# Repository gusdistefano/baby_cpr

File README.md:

# Neonatal CPR Simulator

This repository is available in multiple languages:

- [English](README_EN.md)

- [Español](README_ES.md)

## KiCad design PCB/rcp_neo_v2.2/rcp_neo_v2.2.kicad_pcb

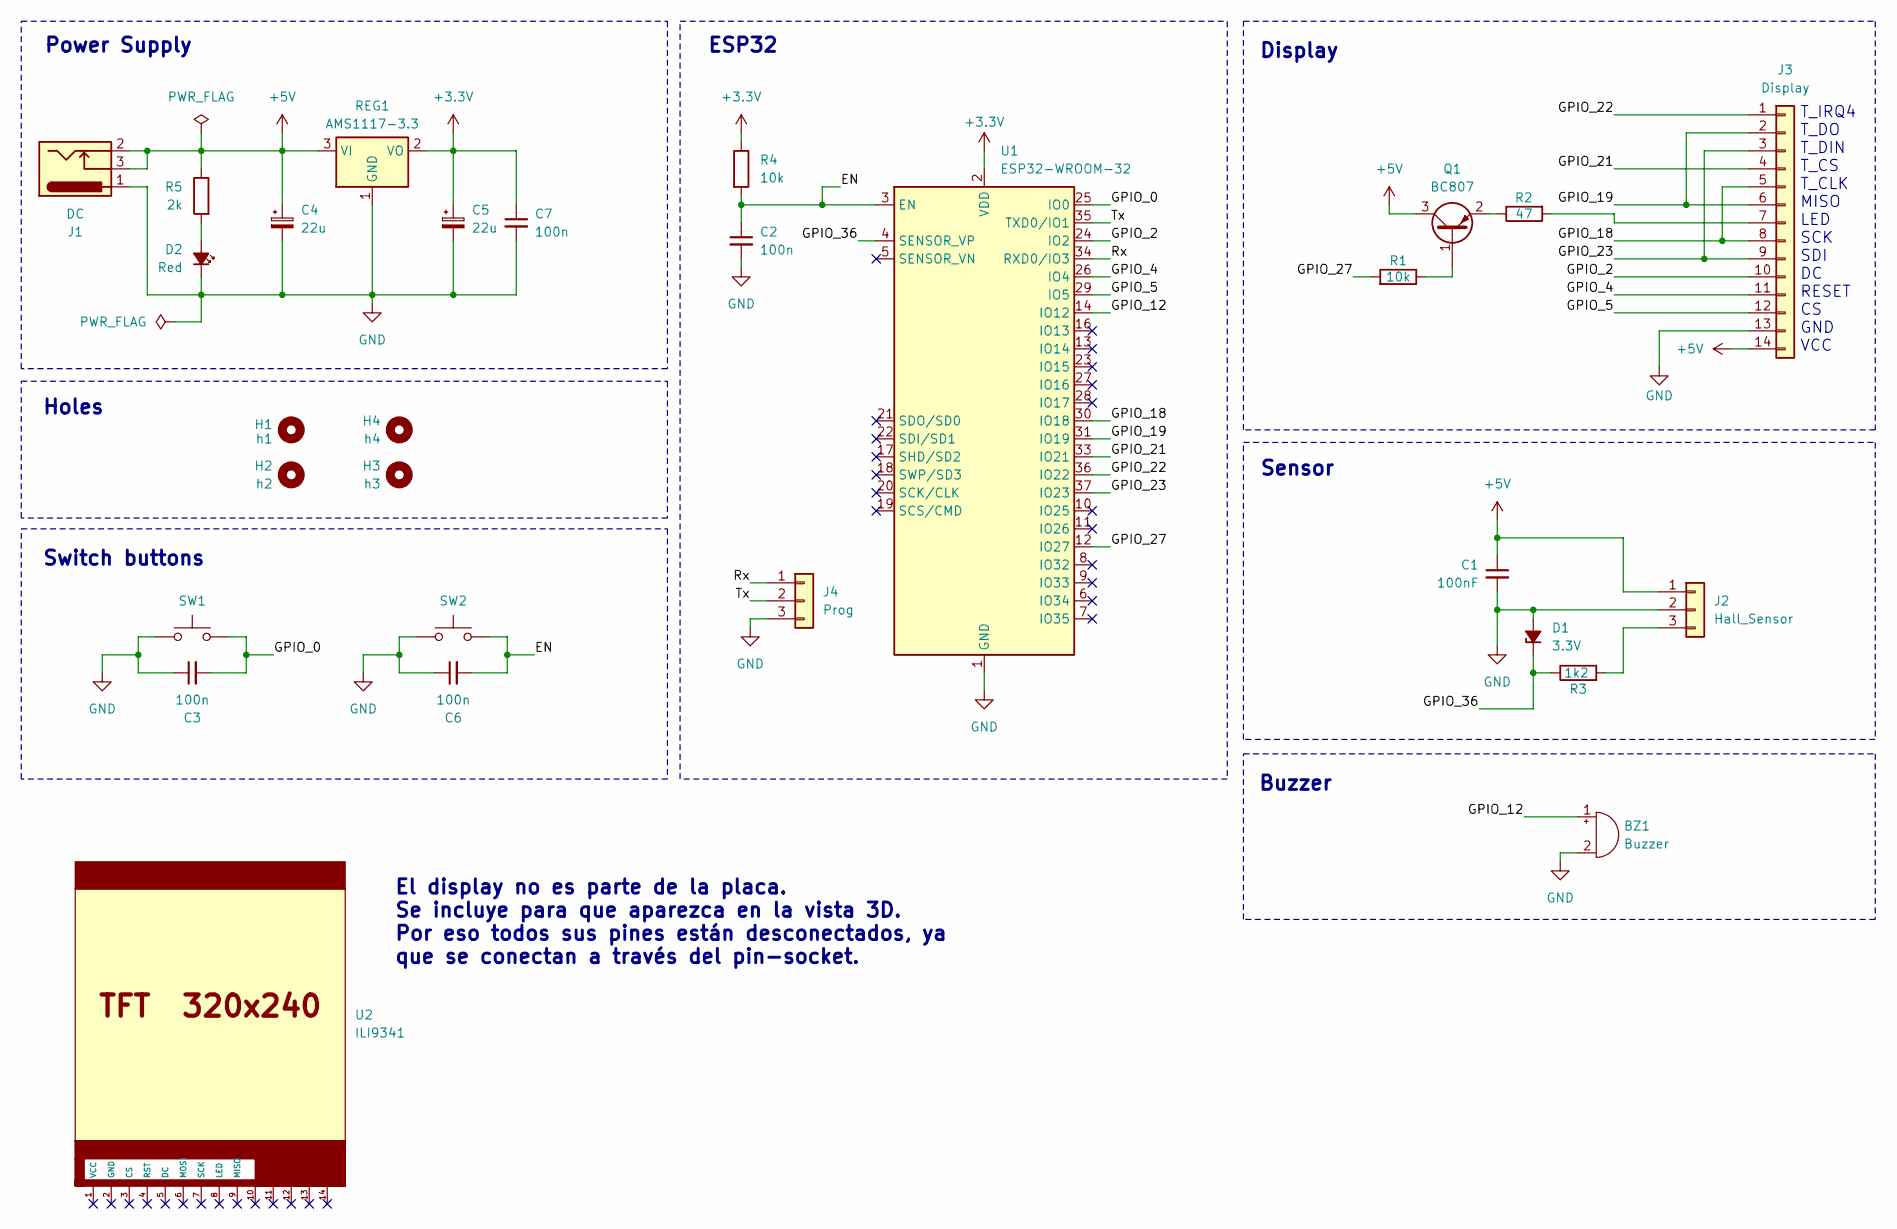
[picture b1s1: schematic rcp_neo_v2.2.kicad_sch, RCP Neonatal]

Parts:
BZ1: Buzzer; Buzzer_12x9.5RM7.6
C1: 100nF; C_1206_3216Metric_Pad1.33x1.80mm_HandSolder
C2, C3, C6, C7: 100n; C_1206_3216Metric_Pad1.33x1.80mm_HandSolder
C4, C5: 22u; CP_Elec_5x4.4
D1: 3.3V; D_DO-35_SOD27_P7.62mm_Horizontal
D2: Red; LED_D3.0mm_Horizontal_O1.27mm_Z2.0mm
H1: h1; MountingHole_3mm
H2: h2; MountingHole_3mm
H3: h3; MountingHole_3mm
H4: h4; MountingHole_3mm
J1: DC; BarrelJack_Horizontal
J2: Hall_Sensor; PinHeader_1x03_P2.54mm_Horizontal
J3: Display; PinSocket_1x14_P2.54mm_Vertical
J4: Prog; PinHeader_1x03_P2.54mm_Horizontal
Q1: BC807; SOT-23
R1, R4: 10k; R_1206_3216Metric_Pad1.30x1.75mm_HandSolder
R2: 47; R_1206_3216Metric_Pad1.30x1.75mm_HandSolder
R3: 1k2; R_1206_3216Metric_Pad1.30x1.75mm_HandSolder
R5: 2k; R_1206_3216Metric_Pad1.30x1.75mm_HandSolder
REG1: AMS1117-3.3; SOT-223-3_TabPin2
SW1, SW2: SW_Push; SW_SPST_B3U-1000P
U1: ESP32-WROOM-32
U2: ILI9341; TFT-320x240_ILI9341_TOUCH

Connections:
+3.3V: C5.1, C7.1, R4.1, REG1.2 (VO), U1.2 (VDD)
+5V: C1.1, C4.1, J1.2, J1.3, J2.1, J3.14, Q1.3 (C), R5.1, REG1.3 (VI)
/EN: C2.1, C6.2, R4.2, SW2.2, U1.3 (EN)
/GPIO_0: C3.2, SW1.2, U1.25 (IO0)
/GPIO_2: J3.10, U1.24 (IO2)
/GPIO_4: J3.11, U1.26 (IO4)
/GPIO_5: J3.12, U1.29 (IO5)
/GPIO_12: BZ1.1 (+), U1.14 (IO12)
/GPIO_18: J3.5, J3.8, U1.30 (IO18)
/GPIO_19: J3.2, J3.6, U1.31 (IO19)
/GPIO_21: J3.4, U1.33 (IO21)
/GPIO_22: J3.1, U1.36 (IO22)
/GPIO_23: J3.3, J3.9, U1.37 (IO23)
/GPIO_27: R1.2, U1.12 (IO27)
/GPIO_36: D1.1 (K), R3.1, U1.4 (SENSOR_VP)
/Rx: J4.1, U1.34 (RXD0/IO3)
/Tx: J4.2, U1.35 (TXD0/IO1)
GND: BZ1.2 (-), C1.2, C2.2, C3.1, C4.2, C5.2, C6.1, C7.2, D1.2 (A), D2.1 (K), J1.1, J2.2, J3.13, J4.3, REG1.1 (GND), SW1.1, SW2.1, U1.1 (GND), U1.15 (GND), U1.38 (GND), U1.39 (GND)
unnamed: D2.2 (A), R5.2
unnamed: J2.3, R3.2
unnamed: J3.7, R2.2
unnamed: Q1.1 (B), R1.1
unnamed: Q1.2 (E), R2.1

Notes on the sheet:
ESP32
El display no es parte de la placa. Se incluye para que aparezca en la vista 3D. Por eso todos sus pines están desconectados, ya que se conectan a través del pin-socket.
Buzzer
Switch buttons
Sensor
Display
T_IRQ4 T_DO T_DIN T_CS T_CLK MISO LED SCK SDI DC RESET CS GND VCC
Holes
Power Supply

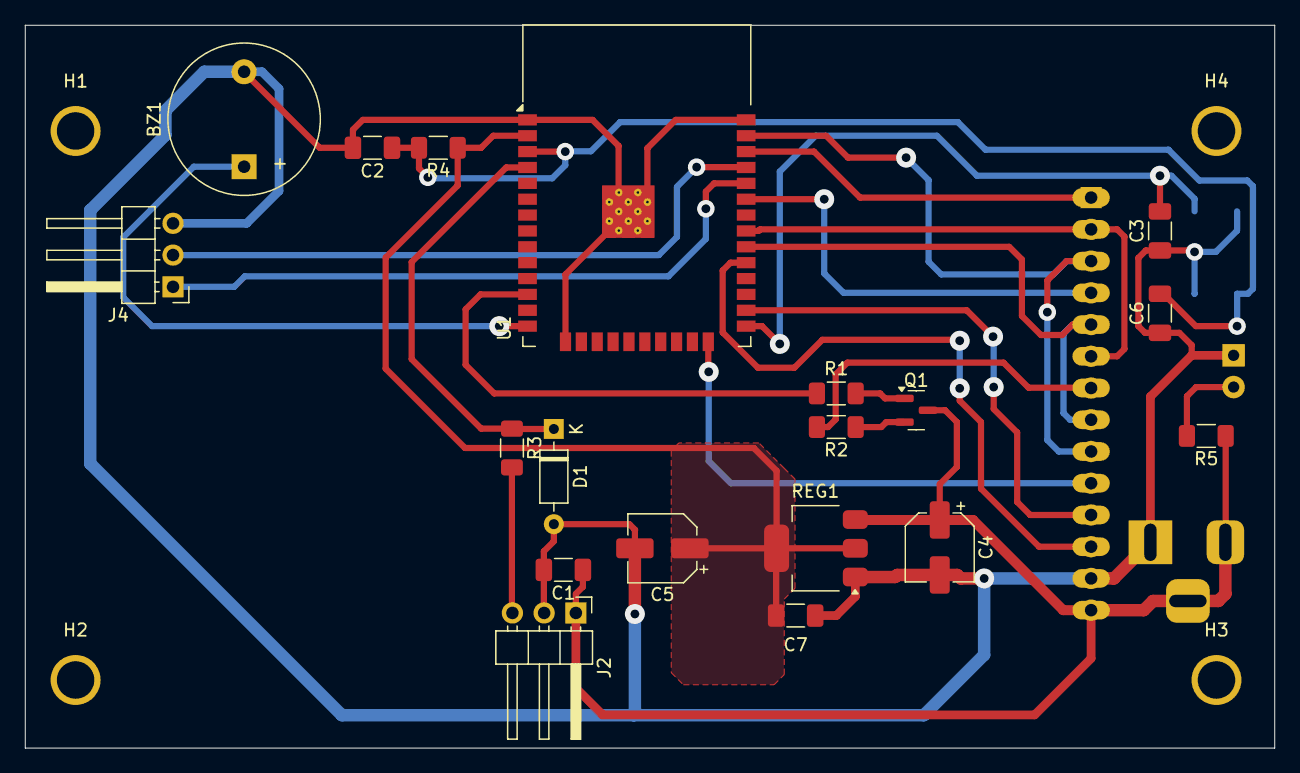
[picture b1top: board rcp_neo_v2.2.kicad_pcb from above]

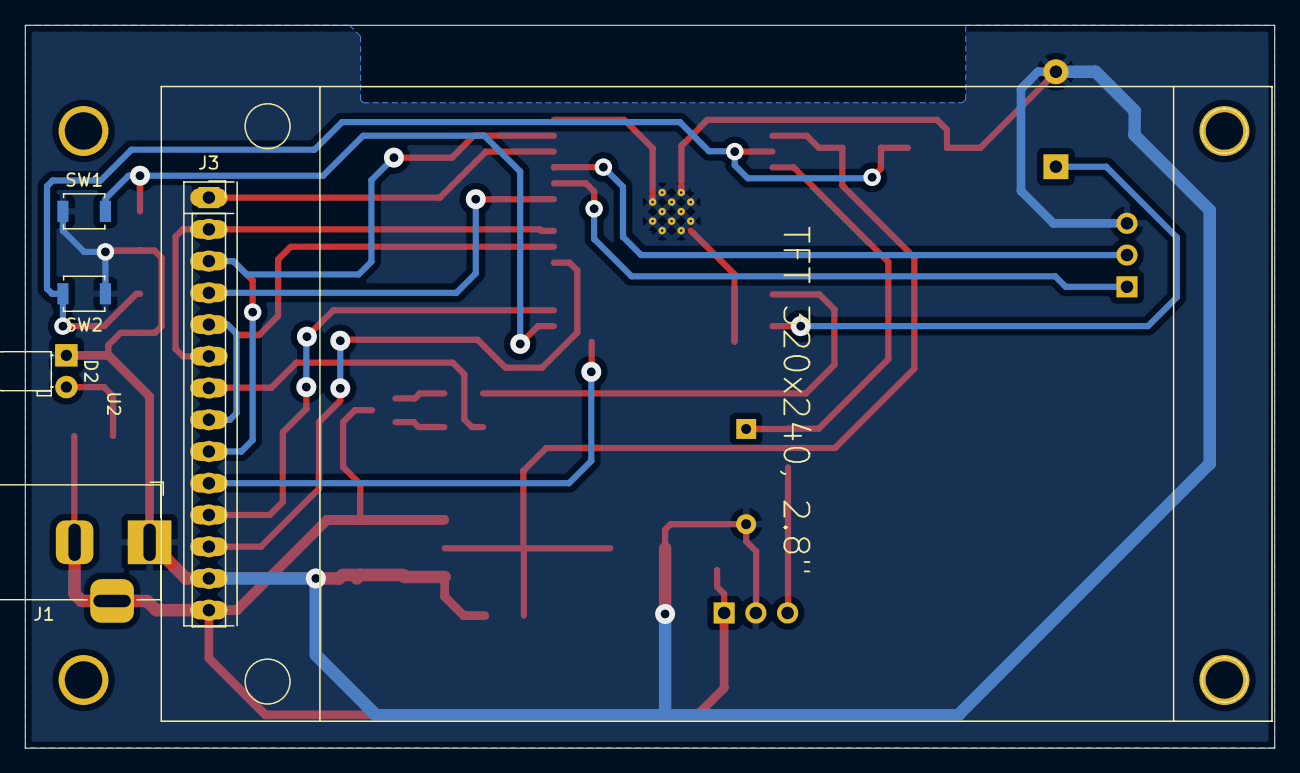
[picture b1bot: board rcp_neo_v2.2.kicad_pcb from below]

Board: 2 copper layers, 100.0 x 57.9 mm, 29 parts (6 on the bottom side), 23 nets.

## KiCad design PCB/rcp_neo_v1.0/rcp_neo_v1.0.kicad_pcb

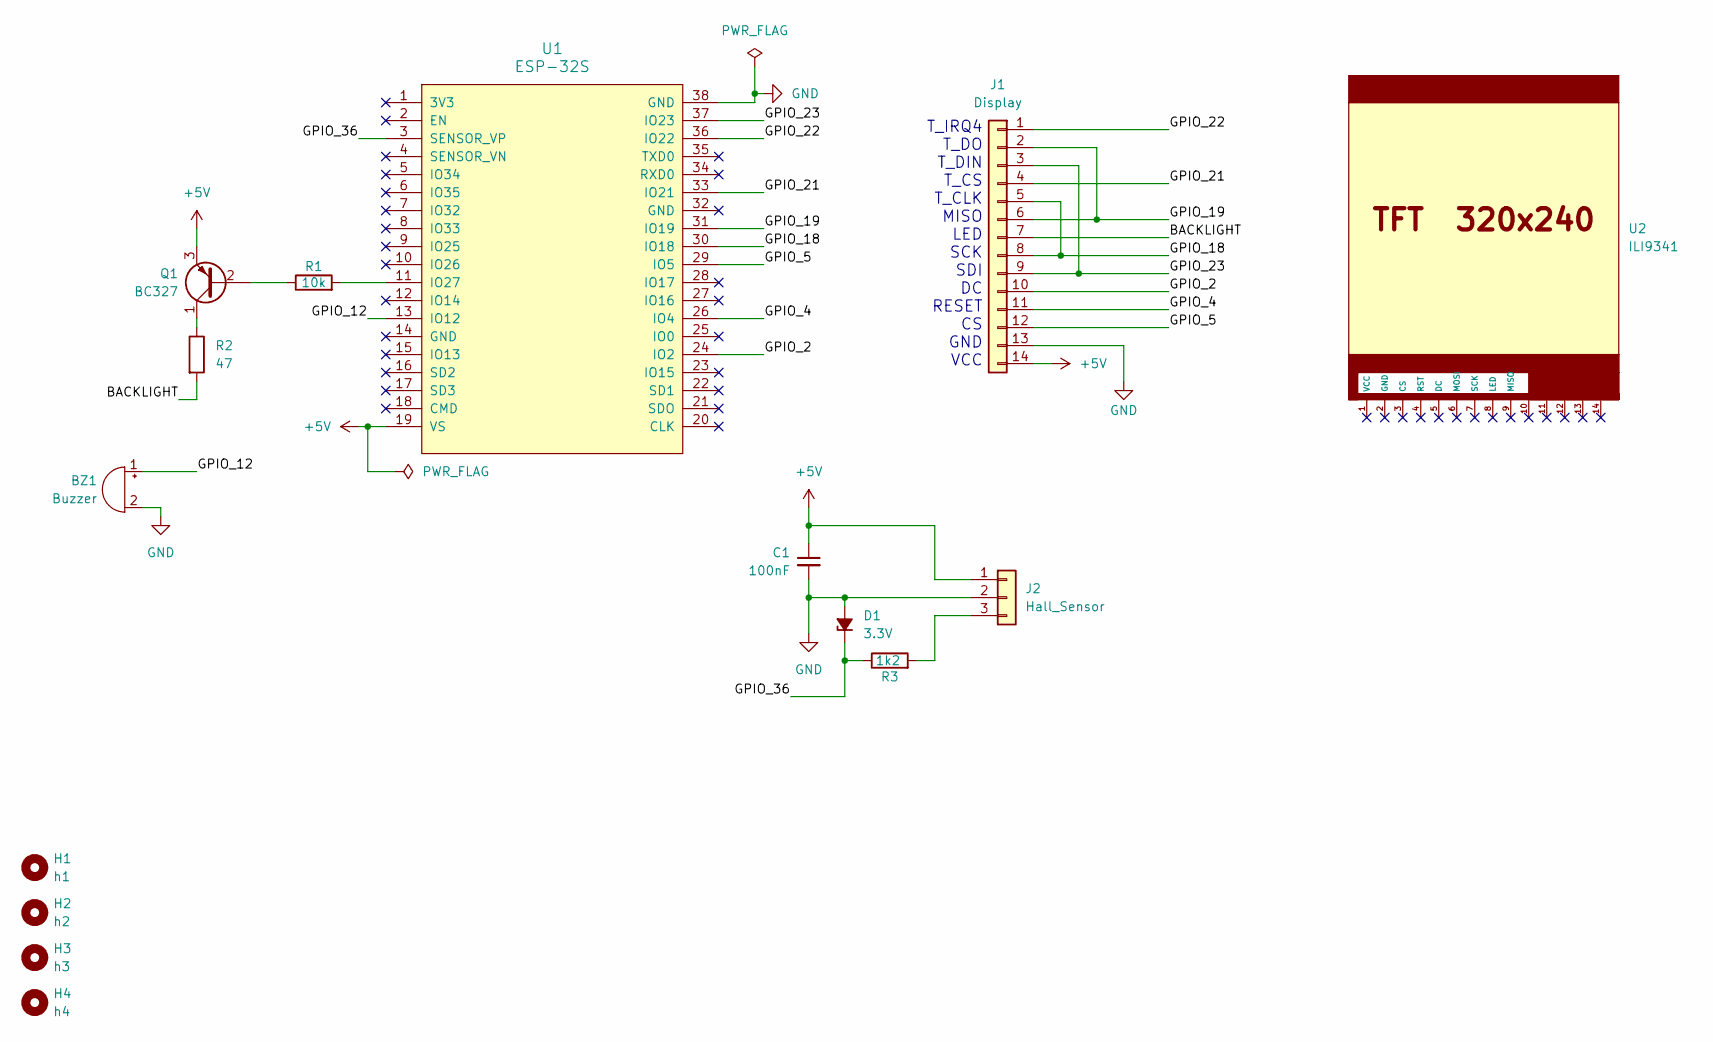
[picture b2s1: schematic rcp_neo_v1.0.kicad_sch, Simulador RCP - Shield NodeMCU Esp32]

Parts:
BZ1: Buzzer; Buzzer_12x9.5RM7.6
C1: 100nF; C_Disc_D5.0mm_W2.5mm_P5.00mm
D1: 3.3V; D_DO-35_SOD27_P7.62mm_Horizontal
H1: h1; MountingHole_3mm
H2: h2; MountingHole_3mm
H3: h3; MountingHole_3mm
H4: h4; MountingHole_3mm
J1: Display; PinSocket_1x14_P2.54mm_Vertical_SMD_Pin1Left
J2: Hall_Sensor; PinHeader_1x03_P2.54mm_Vertical
Q1: BC327; TO-92_Inline_Wide
R1: 10k; R_Axial_DIN0207_L6.3mm_D2.5mm_P7.62mm_Horizontal
R2: 47; R_Axial_DIN0207_L6.3mm_D2.5mm_P7.62mm_Horizontal
R3: 1k2; R_Axial_DIN0207_L6.3mm_D2.5mm_P7.62mm_Horizontal
U1: ESP-32S; Esp32-S_Wroom32Module_38pins
U2: ILI9341; TFT-320x240_ILI9341_TOUCH

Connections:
+5V: C1.1, J1.14, J2.1, Q1.3 (E), U1.19 (VS)
/BACKLIGHT: J1.7, R2.2
/GPIO_2: J1.10, U1.24 (IO2)
/GPIO_4: J1.11, U1.26 (IO4)
/GPIO_5: J1.12, U1.29 (IO5)
/GPIO_12: BZ1.1 (+), U1.13 (IO12)
/GPIO_18: J1.5, J1.8, U1.30 (IO18)
/GPIO_19: J1.2, J1.6, U1.31 (IO19)
/GPIO_21: J1.4, U1.33 (IO21)
/GPIO_22: J1.1, U1.36 (IO22)
/GPIO_23: J1.3, J1.9, U1.37 (IO23)
/GPIO_36: D1.1 (K), R3.1, U1.3 (SENSOR_VP)
GND: BZ1.2 (-), C1.2, D1.2 (A), J1.13, J2.2, U1.38 (GND)
unnamed: J2.3, R3.2
unnamed: Q1.2 (B), R1.1
unnamed: Q1.1 (C), R2.1
unnamed: R1.2, U1.11 (IO27)

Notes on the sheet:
T_IRQ4 T_DO T_DIN T_CS T_CLK MISO LED SCK SDI DC RESET CS GND VCC

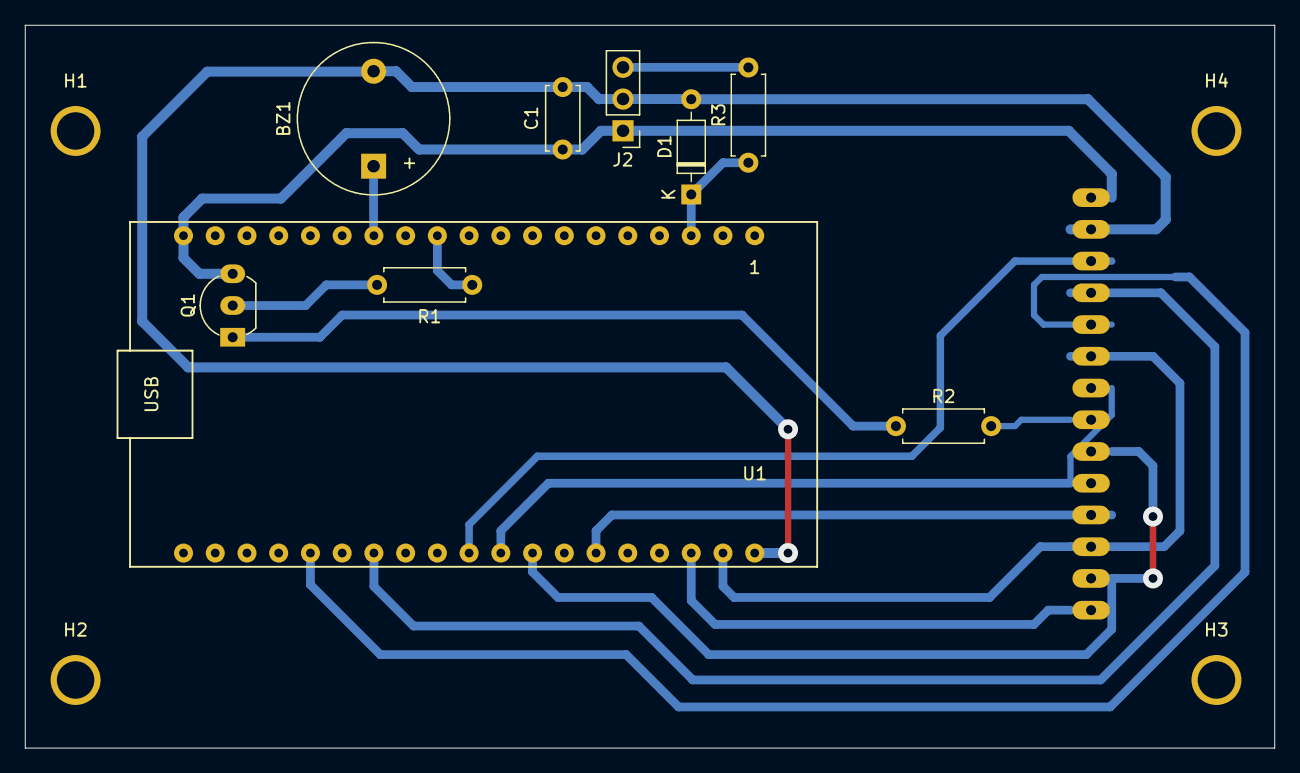
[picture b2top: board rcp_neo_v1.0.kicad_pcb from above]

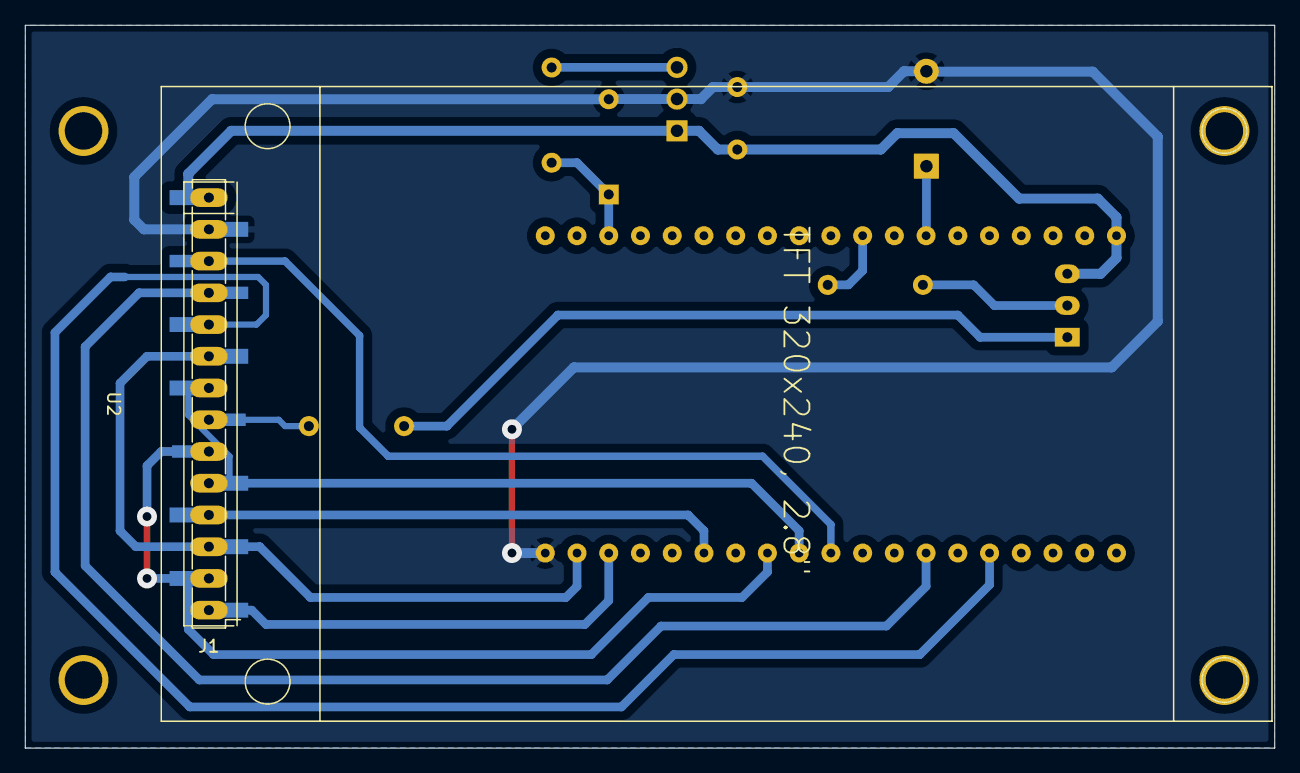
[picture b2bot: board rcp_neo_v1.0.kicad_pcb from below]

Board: 2 copper layers, 100.0 x 57.9 mm, 15 parts (2 on the bottom side), 17 nets.

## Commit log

2025-02-04 Final version of Neonatal CPR Simulator app
2025-02-05 Add documentation generated with Doxygen and Datasheets
2025-03-24 Eliminacion de comentarios debugging - componente hall_sensor
